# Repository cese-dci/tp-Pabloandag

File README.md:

Repositorio correspondiente al TP final de la materia Diseño de Circuitos Impresos

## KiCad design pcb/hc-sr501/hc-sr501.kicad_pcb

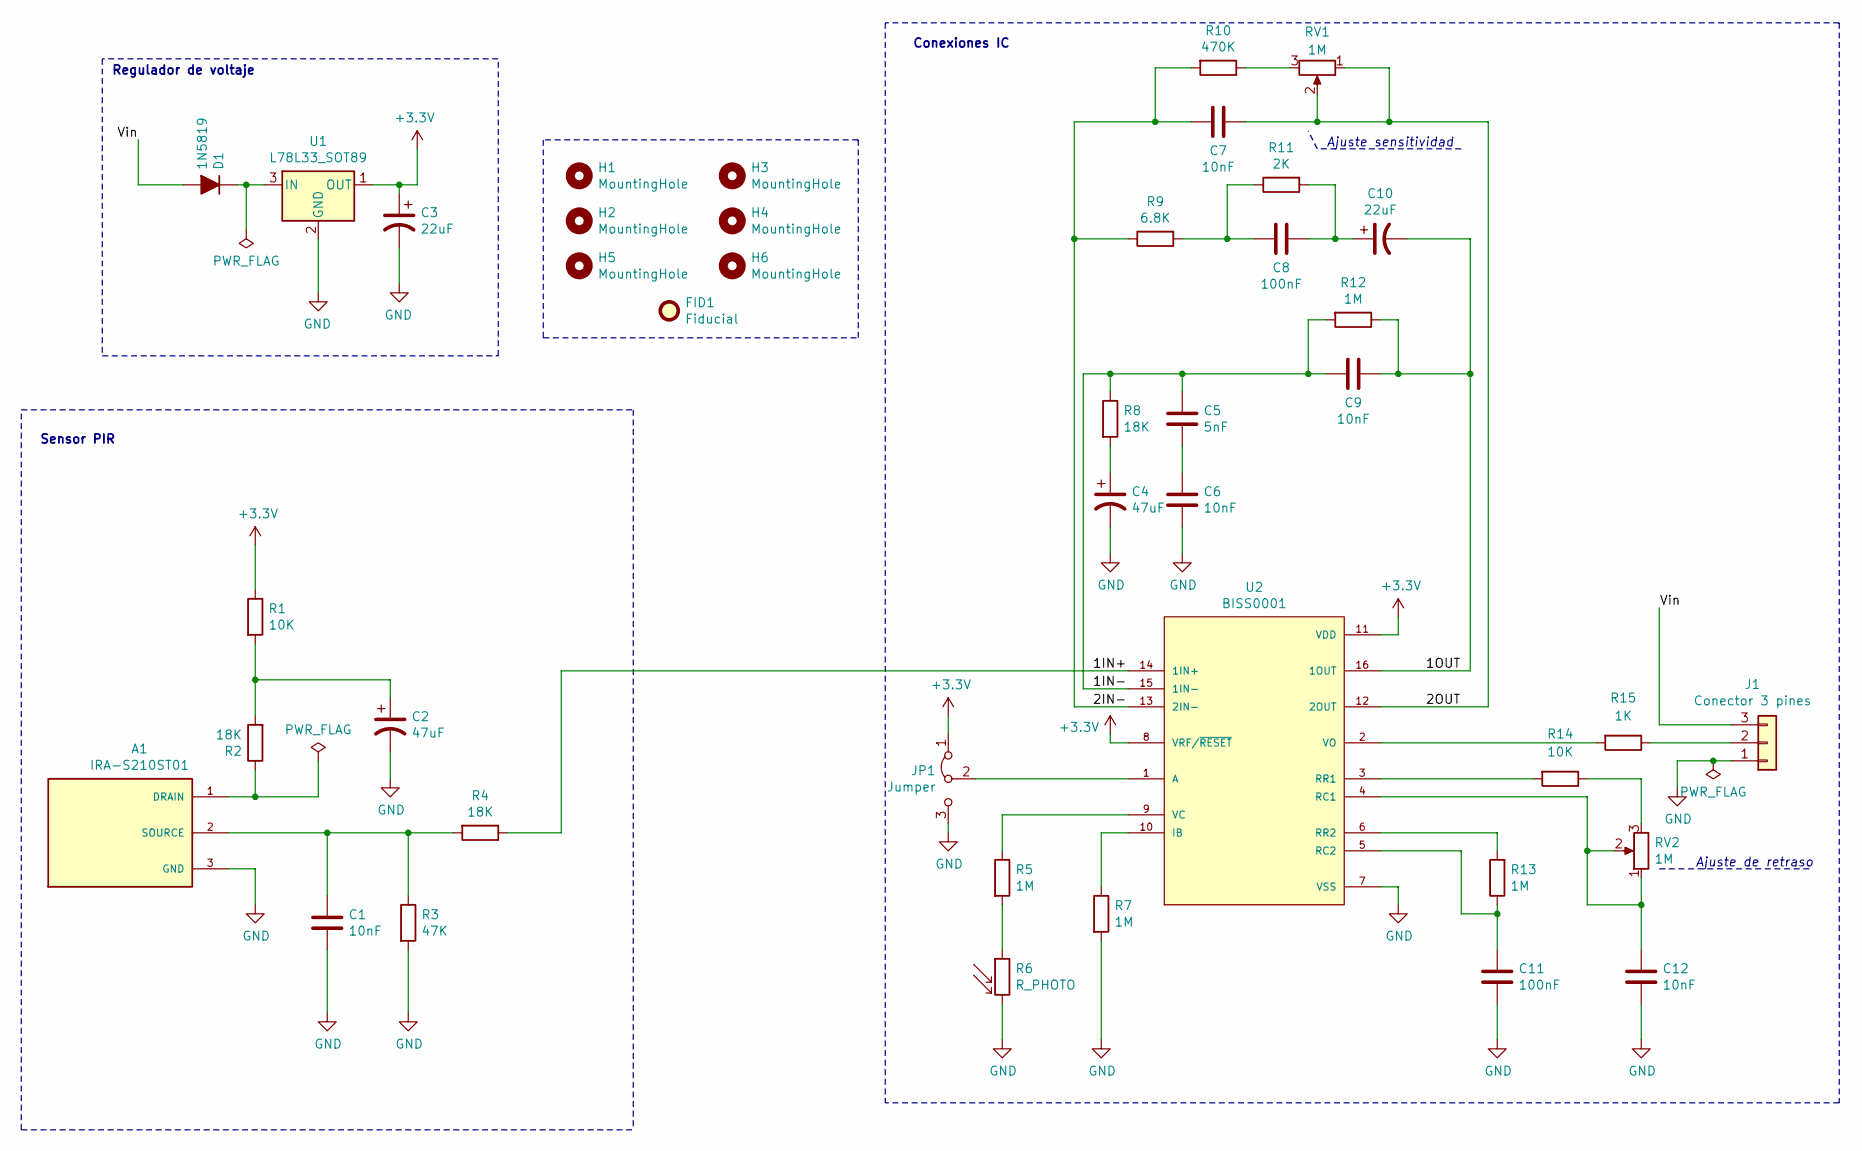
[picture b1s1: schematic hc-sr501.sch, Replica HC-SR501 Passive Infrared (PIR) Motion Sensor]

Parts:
A1: IRA-S210ST01; TO254P940H490-3; Digi-Key Part Number 490-11915-ND
C1, C6, C7, C9, C12: 10nF; C_0805_2012Metric_Pad1.18x1.45mm_HandSolder
C2, C4: 47uF; CP_Radial_D4.0mm_P2.00mm
C3, C10: 22uF; CP_Radial_D4.0mm_P2.00mm
C5: 5nF; C_0805_2012Metric_Pad1.18x1.45mm_HandSolder
C8, C11: 100nF; C_0805_2012Metric_Pad1.18x1.45mm_HandSolder
D1: 1N5819; D_MiniMELF; Digi-Key Part Number 1N5819MDICT-ND
FID1: Fiducial; Fiducial_0.5mm_Mask1mm
H1, H2, H3, H4: MountingHole; MountingHole_1mm
H5, H6: MountingHole; MountingHole_2.1mm
J1: Conector 3 pines; PinHeader_1x03_P2.00mm_Vertical
JP1: Jumper; SolderJumper-3_P1.3mm_Open_Pad1.0x1.5mm_NumberLabels
R1, R14: 10K; R_0805_2012Metric_Pad1.20x1.40mm_HandSolder
R2, R4, R8: 18K; R_0805_2012Metric_Pad1.20x1.40mm_HandSolder
R3: 47K; R_0805_2012Metric_Pad1.20x1.40mm_HandSolder
R5, R7, R12, R13: 1M; R_0805_2012Metric_Pad1.20x1.40mm_HandSolder
R6: R_PHOTO; R_0805_2012Metric_Pad1.20x1.40mm_HandSolder
R9: 6.8K; R_0805_2012Metric_Pad1.20x1.40mm_HandSolder
R10: 470K; R_0805_2012Metric_Pad1.20x1.40mm_HandSolder
R11: 2K; R_0805_2012Metric_Pad1.20x1.40mm_HandSolder
R15: 1K; R_0805_2012Metric_Pad1.20x1.40mm_HandSolder
RV1, RV2: 1M; Potentiometer_Bourns_3362Z_Horizontal; Digi-Key Part Number 3362Z-1-105-ND
U1: L78L33_SOT89; SOT-89-3; Digi-Key Part Number 497-7286-2-ND
U2: BISS0001; SOIC127P600X180-16N; Mouser N 485-189

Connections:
+3V3: C3.1, JP1.1 (A), R1.1, U1.1 (OUT), U2.8 (VRF/~RESET), U2.11 (VDD)
/1IN+: R4.1, U2.14 (1IN+)
/1IN-: C5.1, C9.2, R8.1, R12.2, U2.15 (1IN-)
/1OUT: C9.1, C10.2, R12.1, U2.16 (1OUT)
/2IN-: C7.2, R9.1, R10.2, U2.13 (2IN-)
/2OUT: C7.1, RV1.1, RV1.2, U2.12 (2OUT)
/Vin: D1.2 (A), J1.3
GND: A1.3 (GND), C1.2, C2.2, C3.2, C4.2, C6.2, C11.2, C12.2, J1.1, JP1.3 (B), R3.2, R6.2, R7.2, U1.2 (GND), U2.7 (VSS)
unnamed: A1.1 (DRAIN), R2.1
unnamed: A1.2 (SOURCE), C1.1, R3.1, R4.2
unnamed: C2.1, R1.2, R2.2
unnamed: C4.1, R8.2
unnamed: C5.2, C6.1
unnamed: C8.1, R9.2, R11.1
unnamed: C8.2, C10.1, R11.2
unnamed: C11.1, R13.1, U2.5 (RC2)
unnamed: C12.1, RV2.1, RV2.2, U2.4 (RC1)
unnamed: D1.1 (K), U1.3 (IN)
unnamed: J1.2, R15.1
unnamed: JP1.2 (C), U2.1 (A)
unnamed: R5.1, U2.9 (VC)
unnamed: R5.2, R6.1
unnamed: R7.1, U2.10 (IB)
unnamed: R10.1, RV1.3
unnamed: R13.2, U2.6 (RR2)
unnamed: R14.1, RV2.3
unnamed: R14.2, U2.3 (RR1)
unnamed: R15.2, U2.2 (VO)

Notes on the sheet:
Sensor PIR
Regulador de voltaje
Ajuste de retraso
Ajuste sensitividad
Conexiones IC

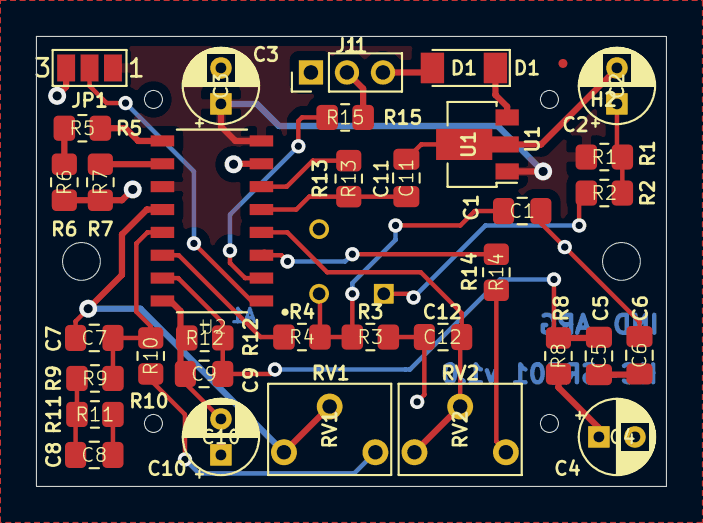
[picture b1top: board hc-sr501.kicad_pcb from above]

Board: 2 copper layers, 35.0 x 25.0 mm, 42 parts (1 on the bottom side), 28 nets.

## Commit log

2021-04-12 Avance esquemático
2021-04-13 Terminado esquematico y asociaciones de footprints
2021-04-13 Terminado PCB
2021-04-14 Prueba manejo de librerias
2021-04-14 Agrego datasheet BISS0001
2021-04-14 Prueba ordenar librerias
2021-04-14 Arreglado manejo de librerias
2021-04-21 Cambios de PCB
2021-04-23 PCB completo sin montaje
2021-04-26 Last commit

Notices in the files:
pcb/hc-sr501/hc-sr501.kicad_pcb:
Released under the Creative Commons Attribution Share-Alike 4.0 Licence
pcb/hc-sr501/hc-sr501.sch:
Creative Commons Attribution ShareAlike 4.0 International License
